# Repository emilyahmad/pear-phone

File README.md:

# Pear phone

Recreating the pear phones from Victorious
Touch screen with a pear shaped case, a home screen and off button.
Some apps, plus posting to the slap.com

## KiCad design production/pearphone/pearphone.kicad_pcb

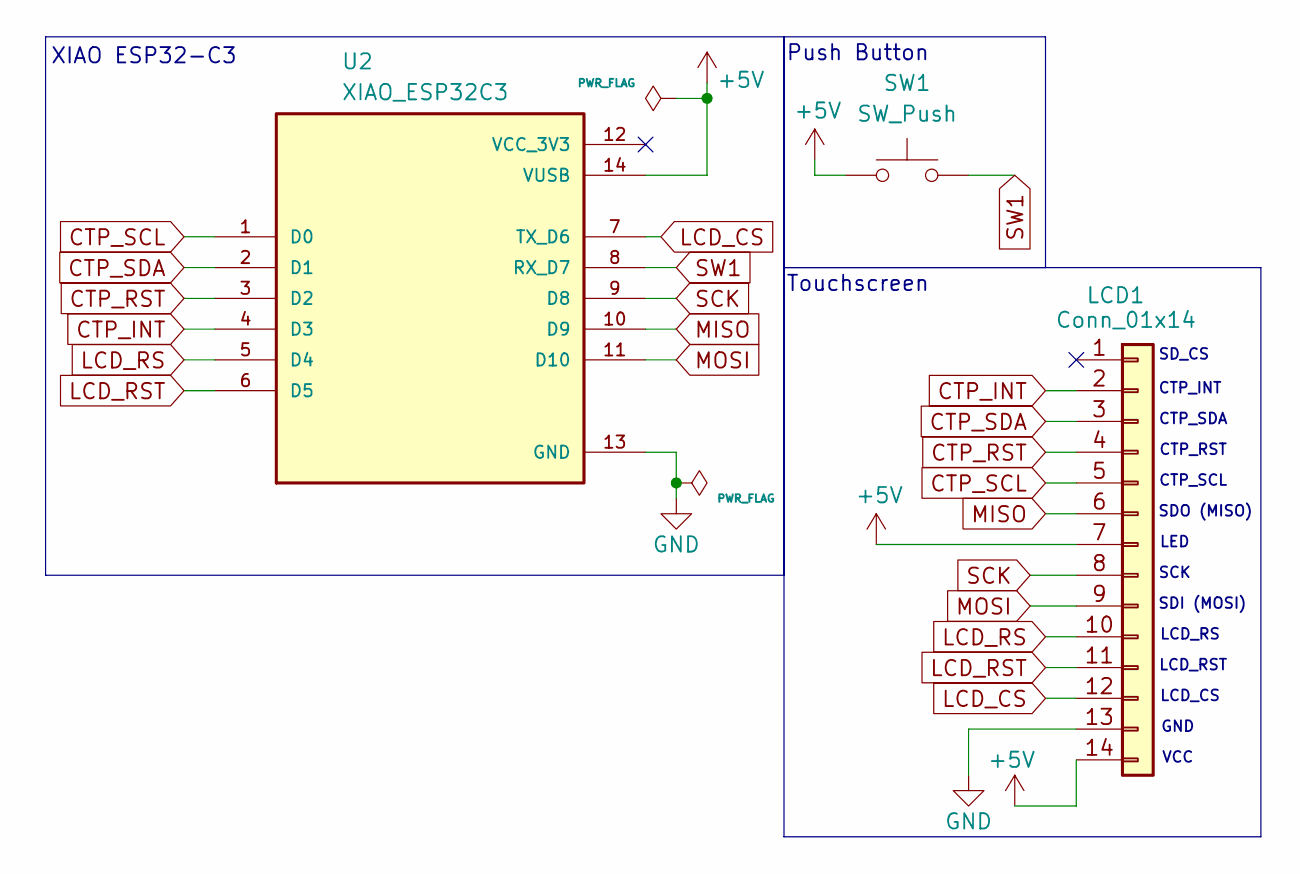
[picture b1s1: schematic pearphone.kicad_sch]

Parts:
LCD1: Conn_01x14; PinSocket_1x14_P2.54mm_Vertical
SW1: SW_Push; SW_PUSH_6mm
U2: XIAO_ESP32C3; MODULE_XIAO_ESP32C3; PARTREV 23/05/2022

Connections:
+5V: LCD1.7, LCD1.14, SW1.1, U2.14 (VUSB)
CTP_INT: LCD1.2, U2.4 (D3)
CTP_RST: LCD1.4, U2.3 (D2)
CTP_SCL: LCD1.5, U2.1 (D0)
CTP_SDA: LCD1.3, U2.2 (D1)
GND: LCD1.13, U2.13 (GND)
LCD_CS: LCD1.12, U2.7 (TX_D6)
LCD_RS: LCD1.10, U2.5 (D4)
LCD_RST: LCD1.11, U2.6 (D5)
MISO: LCD1.6, U2.10 (D9)
MOSI: LCD1.9, U2.11 (D10)
SCK: LCD1.8, U2.9 (D8)
SW1: SW1.2, U2.8 (RX_D7)

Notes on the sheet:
SD_CS
CTP_SDA
LED
SDI (MOSI)
LCD_CS
LCD_RS
SDO (MISO)
GND
SCK
CTP_RST
CTP_INT
Push Button
Touchscreen
VCC
XIAO ESP32-C3
CTP_SCL
LCD_RST

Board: 2 copper layers, 3 parts (0 on the bottom side), 13 nets, no tracks yet.

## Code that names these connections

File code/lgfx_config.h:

// LovyanGFX custom config for:
//   Board:   Seeed XIAO ESP32-C3
//   Display: Hosyond 2.8" IPS 240x320, ILI9341V driver, 4-line SPI
//   Touch:   FT6336G capacitive, I2C
//
// Pin mapping used (XIAO D-label -> real ESP32-C3 GPIO):
//   LCD_RS(DC) D4 -> GPIO6    LCD_RST D5 -> GPIO7    LCD_CS  D6 -> GPIO21
//   LED(BL)    D7 -> GPIO20   SCK     D8 -> GPIO8    MISO    D9 -> GPIO9
//   MOSI       D10 -> GPIO10
//   CTP_SCL    D0 -> GPIO2    CTP_SDA D1 -> GPIO3    CTP_RST D2 -> GPIO4
//   CTP_INT    D3 -> GPIO5

#pragma once
#define LGFX_USE_V1
#include <LovyanGFX.hpp>

class LGFX : public lgfx::LGFX_Device
{
  lgfx::Panel_ILI9341 _panel_instance;
  lgfx::Bus_SPI        _bus_instance;
  lgfx::Light_PWM      _light_instance;
  lgfx::Touch_FT5x06   _touch_instance;   // covers FT6206/FT6236/FT6336/FT6436

public:
  LGFX(void)
  {
    { // ---- SPI bus (shared by the display) ----
      auto cfg = _bus_instance.config();

      cfg.spi_host   = SPI2_HOST;    // ESP32-C3: use SPI2_HOST or SPI3_HOST (not VSPI/HSPI)
      cfg.spi_mode   = 0;
      cfg.freq_write = 40000000;
      cfg.freq_read  = 16000000;
      cfg.spi_3wire  = false;        // this module has a real MISO line, so 4-wire SPI
      cfg.use_lock   = true;
      cfg.dma_channel = SPI_DMA_CH_AUTO;
      cfg.pin_sclk = 8;              // D8 (SCK)
      cfg.pin_mosi = 10;             // D10 (SDI/MOSI)
      cfg.pin_miso = 9;              // D9 (SDO/MISO)
      cfg.pin_dc   = 6;              // D4 (LCD_RS)

      _bus_instance.config(cfg);
      _panel_instance.setBus(&_bus_instance);
    }

    { // ---- Panel ----
      auto cfg = _panel_instance.config();

      cfg.pin_cs  = 21;              // D6 (LCD_CS)
      cfg.pin_rst = 7;               // D5 (LCD_RST)
      cfg.pin_busy = -1;

      cfg.panel_width      = 240;
      cfg.panel_height     = 320;
      cfg.offset_x         = 0;
      cfg.offset_y         = 0;
      cfg.offset_rotation  = 3;
      cfg.dummy_read_pixel = 8;
      cfg.dummy_read_bits  = 1;
      cfg.readable         = true;
      cfg.invert           = true;    // required for IPS panels (this one is IPS)
      cfg.rgb_order        = false;   // set true if red/blue look swapped
      cfg.dlen_16bit        = false;
      cfg.bus_shared         = true;

      _panel_instance.config(cfg);
    }

    { // ---- Backlight ----
      auto cfg = _light_instance.config();

      cfg.pin_bl      = 20;           // D7 (LED)
      cfg.invert      = false;
      cfg.freq        = 44100;
      cfg.pwm_channel = 0;            // C3 only has LEDC channels 0-5, not 7

      _light_instance.config(cfg);
      _panel_instance.setLight(&_light_instance);
    }

    { // ---- Touch (FT6336G, I2C, addr 0x38) ----
      auto cfg = _touch_instance.config();

      cfg.x_min = 0;
      cfg.x_max = 239;
      cfg.y_min = 0;
      cfg.y_max = 319;
      cfg.pin_int    = 5;             // D3 (CTP_INT)
      cfg.pin_rst    = 4;             // D2 (CTP_RST)
      cfg.bus_shared = false;         // touch is on its own I2C bus, not the display's SPI bus
      cfg.offset_rotation = 2;

      cfg.i2c_port = 0;               // ESP32-C3 only has one I2C controller (port 0)
      cfg.i2c_addr = 0x38;            // FT6336G default address
      cfg.pin_sda  = 3;               // D1 (CTP_SDA)
      cfg.pin_scl  = 2;               // D0 (CTP_SCL)
      cfg.freq     = 400000;

      _touch_instance.config(cfg);
      _panel_instance.setTouch(&_touch_instance);
    }

    setPanel(&_panel_instance);
  }
};

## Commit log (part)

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2026-06-19 Add source files
2026-06-19 Want to check if image uploaded in markdown
2026-06-19 Listed some BOM, made prototyping plan
2026-06-19 Organized journals
2026-06-28 Setting up xiao & touchscreen
